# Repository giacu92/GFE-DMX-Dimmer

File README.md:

# DMX-Dimmer
DIY 5 channels dmx dimmer for 4 stage halogen lights.

Get the full assembled board: [http://gfehandmade.bigcartel.com/product/dmx-dimmer-for-4-stage-halogen-lamps](http://giacu92.bigcartel.com/product/dmx-dimmer-for-4-stage-halogen-lamps)

* Author: Giacomo Mammarella
* email: giacu92@gmail.com
* [YouTube video test 1](https://www.youtube.com/watch?v=KfEGCJoeCmY): testing video n1: lamp test
* [YouTube video test 2](https://www.youtube.com/watch?v=TXi1G5LvkLE): testing video n2: strobe and dimming

# About software:
The software is based on a finite state machine. The DMX start address can be choosen on the software  modifying "#define DMX_START_ADDRESS 65".
The DMX channels are currently set like following:
* DMX CHANNEL 65: lamp 1 dimmer (0 -> 100% fade)
* DMX CHANNEL 66: lamp 2 dimmer 
* DMX CHANNEL 67: lamp 3 dimmer 
* DMX CHANNEL 68: lamp 4 dimmer 
* DMX CHANNEL 69: strobo all lamps at chosen speed (40 - 255 strobe from 100ms to 1s)

# _HardwareSerial0.cpp EDIT:_
To let Arduino IDE compile the code we need to do some mods to the _HardwareSerial0.cpp_ file.
On my current Mac OSX Arduino version (1.6.10) the file is placed at the following path:
**Arduino/Contents/Java/hardware/arduino/avr/cores/arduino/HardwareSerial0.cpp**.
Inside it we need to comment out the whole block between line 40 and line 51:
```
/*
#if defined(USART_RX_vect)
  ISR(USART_RX_vect)
#elif defined(USART0_RX_vect)
  ISR(USART0_RX_vect)
#elif defined(USART_RXC_vect)
  ISR(USART_RXC_vect) // ATmega8
#else
  #error "Don't know what the Data Received vector is called for Serial"
#endif
  {
    Serial._rx_complete_irq();
  }
*/
```
That's because we need to tell the Arduino IDE that inside the code we wrote our personal Interrupt Service Routine ("ISR") and we need it to use it in DMX serial communications.
Remember to remove the mods after uploading the code or Serial communications ( like the one we use in Serial.print() ) wont work anymore.

You can find my copy of modded _HardwareSerial0.cpp_ inside the file list.

# File list:
* [DMX_dimmer.brd](https://github.com/giacu92/DMX-Dimmer/blob/master/DMX_dimmer.brd): the Cadsoft Eagle 6.5 board file.
* [DMX_dimmer.sch](https://github.com/giacu92/DMX-Dimmer/blob/master/DMX_dimmer.sch): the Cadsoft Eagle 6.5 schematic file for the board.
* [Code](https://github.com/giacu92/DMX-Dimmer/tree/master/dmx_dimmer): the folder containingh the sketch for the project.
* [HardwareSerial0.cpp](https://github.com/giacu92/DMX-Dimmer/blob/master/HardwareSerial0.cpp): The **MODIFIED** _HardwareSerial0.cpp_ for uploading the code

# Connections:

# Some pics:
Painting the enclosure and test fitting the pcb:

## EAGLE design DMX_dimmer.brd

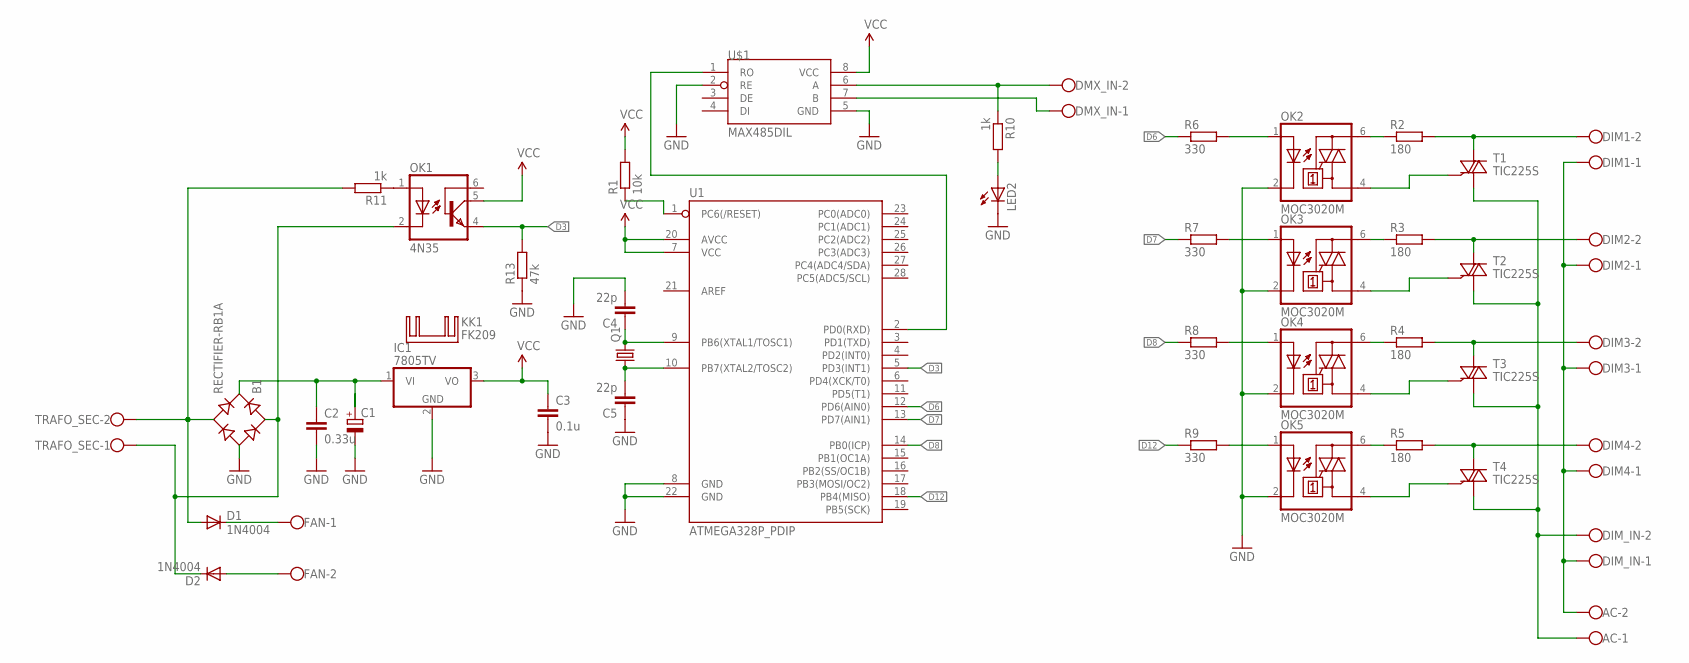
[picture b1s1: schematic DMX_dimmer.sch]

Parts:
AC: W237-102
B1: RECTIFIER-RB1A; RB1A
C1: CPOL-EUE5-10.5; E5-10,5
C2: 0.33u; C050-024X044
C3: 0.1u; C050-024X044
C4, C5: 22p; C025-024X044
D1, D2: 1N4004; DO41-10
DIM1, DIM2, DIM3, DIM4: W237-102
DIM_IN: W237-102
DMX_IN: W237-102
FAN: W237-102
IC1: 7805TV; TO220V
KK1: FK209
LED2: LED3MM
OK1: 4N35; DIL06
OK2, OK3, OK4, OK5: MOC3020M; DIL06
Q1: CRYSTALHC49U-V; HC49U-V
R1: 10k; 0207/7
R2, R3, R4, R5: 180; 0207/2V
R6, R7, R8, R9: 330; 0207/7
R10, R11: 1k; 0207/7
R13: 47k; 0207/7
T1, T2, T3, T4: TIC225S; TO220DS
TRAFO_SEC: W237-102
U1: ATMEGA328P_PDIP; DIL28-3
U$1: MAX485DIL; DIL08

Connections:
D3: OK1.4 (EMI), R13.2, U1.5 (PD3(INT1))
D6: R6.1, U1.12 (PD6(AIN0))
D7: R7.1, U1.13 (PD7(AIN1))
D8: R8.1, U1.14 (PB0(ICP))
D12: R9.1, U1.18 (PB4(MISO))
DIM_IN-1: AC.2, DIM1.1, DIM2.1, DIM3.1, DIM4.1, DIM_IN.1
DIM_IN-2: AC.1, DIM_IN.2, T1.A1, T2.A1, T3.A1, T4.A1
GND: B1.-, C1.-, C2.2, C3.2, C4.2, C5.1, IC1.2 (GND), LED2.K (C), OK2.2 (C), OK3.2 (C), OK4.2 (C), OK5.2 (C), R13.1, U1.8 (GND), U1.22 (GND), U$1.2 (RE), U$1.5 (GND)
unnamed: DIM1.2, R2.2, T1.A2
unnamed: OK2.6 (A2), R2.1
unnamed: DIM2.2, R3.2, T2.A2
unnamed: OK4.1 (A), R8.2
unnamed: OK3.6 (A2), R3.1
unnamed: OK3.1 (A), R7.2
unnamed: DIM4.2, R5.2, T4.A2
unnamed: OK2.1 (A), R6.2
unnamed: OK4.6 (A2), R4.1
unnamed: OK5.6 (A2), R5.1
unnamed: OK5.4 (A1), T4.G
unnamed: OK4.4 (A1), T3.G
unnamed: OK3.4 (A1), T2.G
unnamed: C5.2, Q1.1, U1.10 (PB7(XTAL2/TOSC2))
unnamed: C4.1, Q1.2, U1.9 (PB6(XTAL1/TOSC1))
unnamed: OK2.4 (A1), T1.G
unnamed: DIM3.2, R4.2, T3.A2
unnamed: D1.C, FAN.1
unnamed: D2.A, FAN.2
unnamed: U1.2 (PD0(RXD)), U$1.1 (RO)
unnamed: OK5.1 (A), R9.2
unnamed: LED2.A, R10.2
unnamed: DMX_IN.2, R10.1, U$1.6 (A)
unnamed: DMX_IN.1, U$1.7 (B)
unnamed: OK1.1 (A), R11.1
unnamed: R1.1, U1.1 (PC6(/RESET))
unnamed: B1.AC1, D2.C, OK1.2 (C), TRAFO_SEC.1
unnamed: B1.+, C1.+, C2.1, IC1.1 (VI)
unnamed: B1.AC2, D1.A, R11.2, TRAFO_SEC.2
VCC: C3.1, IC1.3 (VO), OK1.5 (COL), R1.2, U1.7 (VCC), U1.20 (AVCC), U$1.8 (VCC)

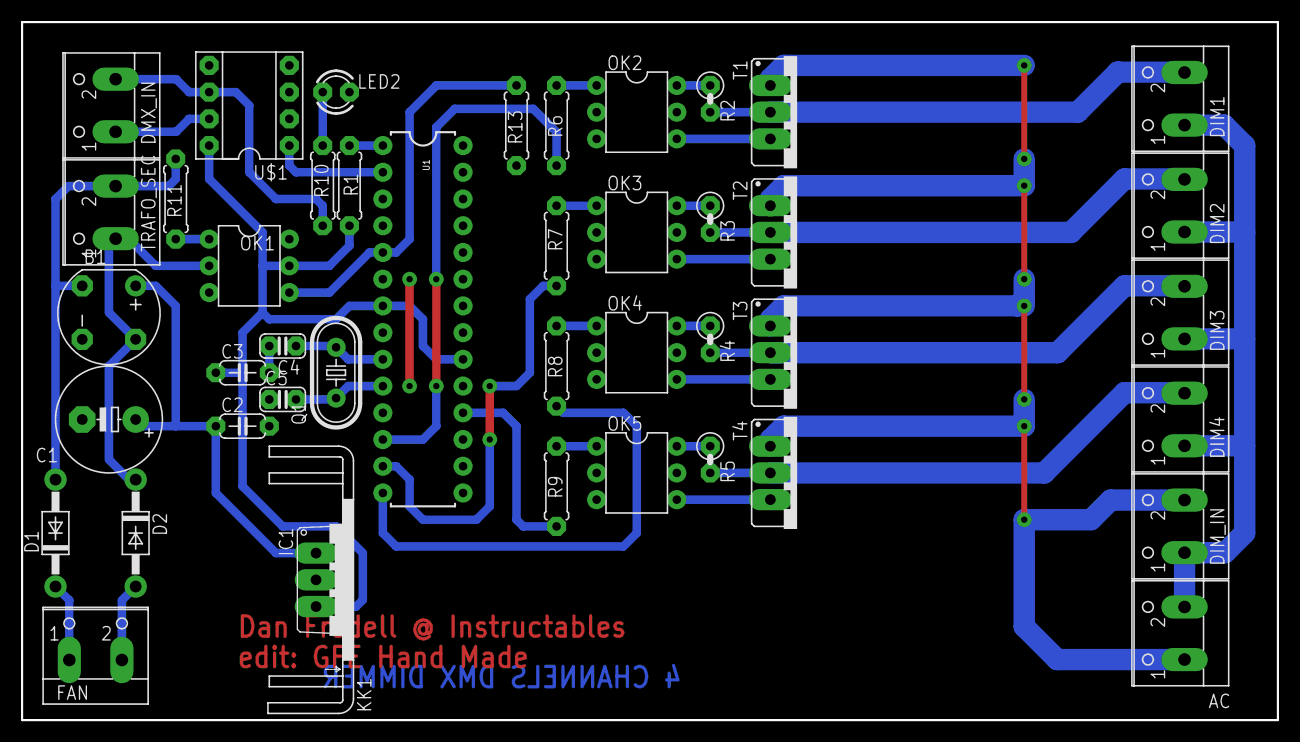
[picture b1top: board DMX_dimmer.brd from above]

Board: 2 copper layers, 119.4 x 66.3 mm, 45 parts (0 on the bottom side), 38 nets.

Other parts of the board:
U$2: LOGO-GRANDE

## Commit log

2016-08-10 Initial commit
    Cadsoft Eagle board, schematic and Arduino code
2016-08-10 Reame.md
    create readme.md
2016-08-31 new firmware
    new firmware released, added strobe effect from 0 to 1000ms
2016-08-31 added strobo
    new firmware, added strobe effect
2016-08-31 added strobe
2016-09-09 Arduino code
    small bug fixes
2016-09-09 Arduino Code
2016-09-13 debug
    fade works, strobo don’t
2016-09-15 v1.0 code
    tested code

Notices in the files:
parts and their libraries:
SparkFun-DigitalIC: Licensing: Creative Commons ShareAlike 4.0 International - https://creativecommons.org/licenses/by-sa/4.0
SparkFun: Licensing: CC v3.0 Share-Alike You are welcome to use this library for commercial purposes.
